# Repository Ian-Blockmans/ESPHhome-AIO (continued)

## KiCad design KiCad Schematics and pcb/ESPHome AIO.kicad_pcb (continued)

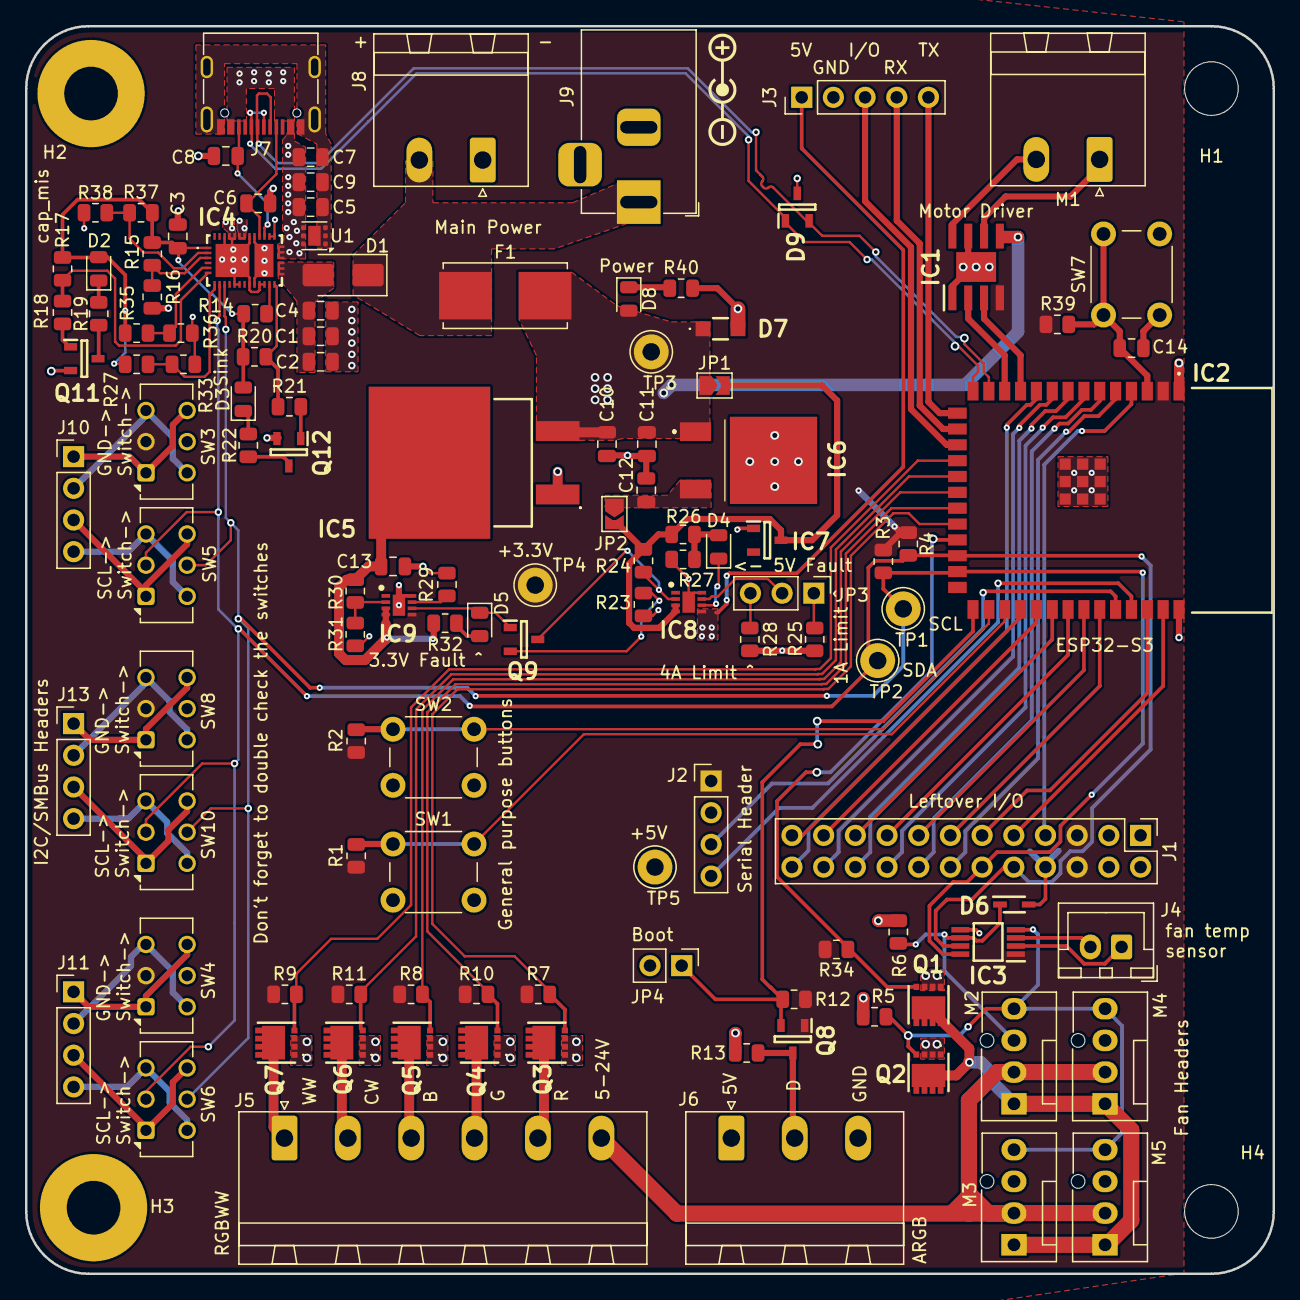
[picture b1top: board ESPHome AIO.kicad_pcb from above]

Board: 2 copper layers, 100.0 x 100.0 mm, 125 parts (0 on the bottom side), 100 nets.

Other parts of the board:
R27#2: 10K; R_0805_2012Metric

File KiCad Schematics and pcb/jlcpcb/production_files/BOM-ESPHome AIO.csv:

Comment,Designator,Footprint,LCSC
330pF,"C6,C8",C_0805_2012Metric,C107115
BZX84-C12,IC7,SOT95P230X110-3N,C108437
D_Zener,D7,HPZRC28QX,C145091
Conn_01x02_Pin,J4,JST_XH_B2B-XH-A_1x02_P2.50mm_Vertical,C158012
10uF,"C1,C10,C13,C2,C3",C_0805_2012Metric,C15850
10nF,"C7,C9",C_0805_2012Metric,C1710
10K,"R1,R12,R13,R18,R2,R21,R23,R3,R31,R39,R4,R40",R_0805_2012Metric,C17414
110k,R15,R_0805_2012Metric,C17422
2.2K,R26,R_0805_2012Metric,C17520
2.32K,R25,R_0805_2012Metric,C17522
20.5K,R30,R_0805_2012Metric,C17537
2K,"R10,R11,R5,R6,R7,R8,R9",R_0805_2012Metric,C17604
487,R28,R_0805_2012Metric,C17718
680,R32,R_0805_2012Metric,C17798
715,R29,R_0805_2012Metric,C17813
"TB67H451FNG,EL",IC1,SOIC127P600X170-9N,C1858375
Fan_4pin,"M2,M3,M4,M5",FanPinHeader_1x04_P2.54mm_Vertical,C240840
Conn_01x04,"J10,J11,J13",PinHeader_1x04_P2.54mm_Vertical,C2718488
LED,"D2,D3,D4,D5",LED_0805_2012Metric,C2833068
ESP32-S3-WROOM-1-N8,IC2,ESP32S3WROOM1N8R8,C2913198
Conn_01x05,J3,PinHeader_1x05_P2.54mm_Vertical,C2935899
USB_C_Receptacle_USB2.0_16P,J7,USB_C_Receptacle_G-Switch_GT-USB-7010ASV,C2965608
36.5K,R24,R_0805_2012Metric,C35928
1uF,"C11,C12,C5",C_0805_2012Metric,C376929
XKB Connection DC-005-5A-3.0,J9,BarrelJack_Horizontal,C388625
100nF,C4,C_0805_2012Metric,C49678
Screw_Terminal_01x03,J6,"PhoenixContact_MSTBA_2,5_3-G-5,08_1x03_P5.08mm_Horizontal",C5187974
Screw_Terminal_01x06,J5,"PhoenixContact_MSTBA_2,5_6-G-5,08_1x06_P5.08mm_Horizontal",C5187977
TVS2200DRV,U1,WSON-6-1EP_2x2mm_P0.65mm_EP1x1.6mm,C523793
Conn_02x12_Odd_Even,J1,PinHeader_2x12_P2.54mm_Vertical,C5383110
EMC2101-ACZL-TR,IC3,SOP65P490X110-8N,C626968
Jumper_3_Bridged12,JP3,PinHeader_1x03_P2.54mm_Vertical,C6332196
Conn_01x04,J2,PinHeader_1x04_P2.54mm_Vertical,C6332197
D_Schottky,D1,D_SMA,C669017
2N7002NXAKR,Q8,SOT95P230X110-3N,C71533
SW_Push,"SW1,SW2,SW7",SW_PUSH_6mm_H7.3mm,C7463311
LD1085D2T33R,IC5,LD1085D2T33R,C7913
Screw_Terminal_01x02,"J8,M1","PhoenixContact_MSTBA_2,5_2-G-5,08_1x02_P5.08mm_Horizontal",C8383
BD50FC0FP-E2,IC6,BD50FC0FPE2,C920705
RQ3E080BNTB,Q6,RQ3E080BNTB,
10K,R27,R_0805_2012Metric,
SW_DPDT_x2,SW4,SW_CK_JS202011CQN_DPDT_Straight,
TPS25730DREFR,IC4,TPS25730DREFR,
5V,TP5,TestPoint_Loop_D2.60mm_Drill1.4mm_Beaded,
10K,R22,R_0805_2012Metric,
SolderJumper_2_Open,JP1,SolderJumper-2_P1.3mm_Open_TrianglePad1.0x1.5mm,
SW_DPDT_x2,SW8,SW_CK_JS202011CQN_DPDT_Straight,
24K,R16,R_0805_2012Metric,
TPS259573DSGR,IC9,SON50P200X200X80-9N,
SCL,TP1,TestPoint_Loop_D2.60mm_Drill1.4mm_Beaded,
2N7002NXAKR,Q9,SOT95P230X110-3N,
SolderJumper_2_Bridged,JP2,SolderJumper-2_P1.3mm_Open_TrianglePad1.0x1.5mm,
SW_DPDT_x2,SW6,SW_CK_JS202011CQN_DPDT_Straight,
MountingHole,H4,MountingHole_4.3mm_M4,
10K,R17,R_0805_2012Metric,
SW_DPDT_x2,SW5,SW_CK_JS202011CQN_DPDT_Straight,
3.3V,TP4,TestPoint_Loop_D2.60mm_Drill1.4mm_Beaded,
RQ3E080BNTB,Q1,RQ3E080BNTB,
MountingHole,H1,MountingHole_4.3mm_M4,
TPS259573DSGR,IC8,SON50P200X200X80-9N,
SW_DPDT_x2,SW10,SW_CK_JS202011CQN_DPDT_Straight,
RQ3E080BNTB,Q2,RQ3E080BNTB,
Fuse,F1,Fuseholder_Littelfuse_Nano2_154x,
RQ3E080BNTB,Q4,RQ3E080BNTB,
MountingHole_Pad,H3,MountingHole_4.3mm_M4_Pad,
10K,R20,R_0805_2012Metric,
SW_DPDT_x2,SW3,SW_CK_JS202011CQN_DPDT_Straight,
RQ3E080BNTB,Q7,RQ3E080BNTB,
Power,TP3,TestPoint_Loop_D2.60mm_Drill1.4mm_Beaded,
MountingHole_Pad,H2,MountingHole_4.3mm_M4_Pad,
10K,R19,R_0805_2012Metric,
RQ3E080BNTB,Q3,RQ3E080BNTB,
SDA,TP2,TestPoint_Loop_D2.60mm_Drill1.4mm_Beaded,
RQ3E080BNTB,Q5,RQ3E080BNTB,
10K,R14,R_0805_2012Metric,
BZX384-C5V1,D6,SOD2512X110N,
10K,R33,R_0805_2012Metric,
110k,R37,R_0805_2012Metric,
1K,R36,R_0805_2012Metric,
Jumper_2_Open,JP4,PinHeader_1x02_P2.54mm_Vertical,
110K,R35,R_0805_2012Metric,
100nF,C14,C_0805_2012Metric,
10K,R34,R_0805_2012Metric,
2N7002NXAKR,Q12,SOT95P230X110-3N,
1K,R38,R_0805_2012Metric,
2N7002NXAKR,Q11,SOT95P230X110-3N,
LED,D8,LED_0805_2012Metric,
ESDALD05UE2X,D9,SOT95P240X115-3N,

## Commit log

2024-02-17 for first upload
2024-02-19 start pcb
2024-02-19 done for the day
2024-02-23 posible V0.1
2024-02-27 v0.1
2024-04-05 backup
2024-06-04 v0.1 prototype ordered
2024-06-04 cleanup
2024-06-18 V0.2 maybe
2024-06-18 create new pdf
2024-06-18 reploted images
2024-07-01 V0.2 wip
